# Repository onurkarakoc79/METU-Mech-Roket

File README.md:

# METU Mech Rocket Team Electronic Cards and Codes
This repository contains the electronic codes and card designs for the METU Mech Rocket Team's rocket system. The system consists of two card designs, each equipped with an Arduino Due controller.

## Communication Card
The first Arduino Due is responsible for communication and utilizes the following modules:

SX1262 LoRa module
SIM800L module
CH376S USB module
The communication card enables data transfer with the ground station. The SX1262 LoRa module and SIM800L module are used for wireless communication, while the CH376S USB module handles data storage to a USB device.

## Processor Card
The second Arduino Due is responsible for data processing and incorporates the following components:

BME280 sensor
Dallas temperature sensor
BMP180 sensor
NEO M8N GPS module
Parachute opening system (controlled by a servo and a transistor that fires the gas tank)
The processor card collects data related to humidity, temperature, altitude, and absolute location. It supports two sensors for each type of data, such as BME280 and BMP180. The collected data is processed using a Kalman filter algorithm for improved accuracy. The processed data is then transferred to the communication card via serial communication.

## Card Designs
This repository also includes the necessary files for the card designs. The provided KiCad files contain the card designs and necessary footprints. To use the designs, add the footprint files to KiCad in the appropriate manner. The card designs have been configured for use with either Arduino Due or Arduino Mega Due, based on the pin configuration.

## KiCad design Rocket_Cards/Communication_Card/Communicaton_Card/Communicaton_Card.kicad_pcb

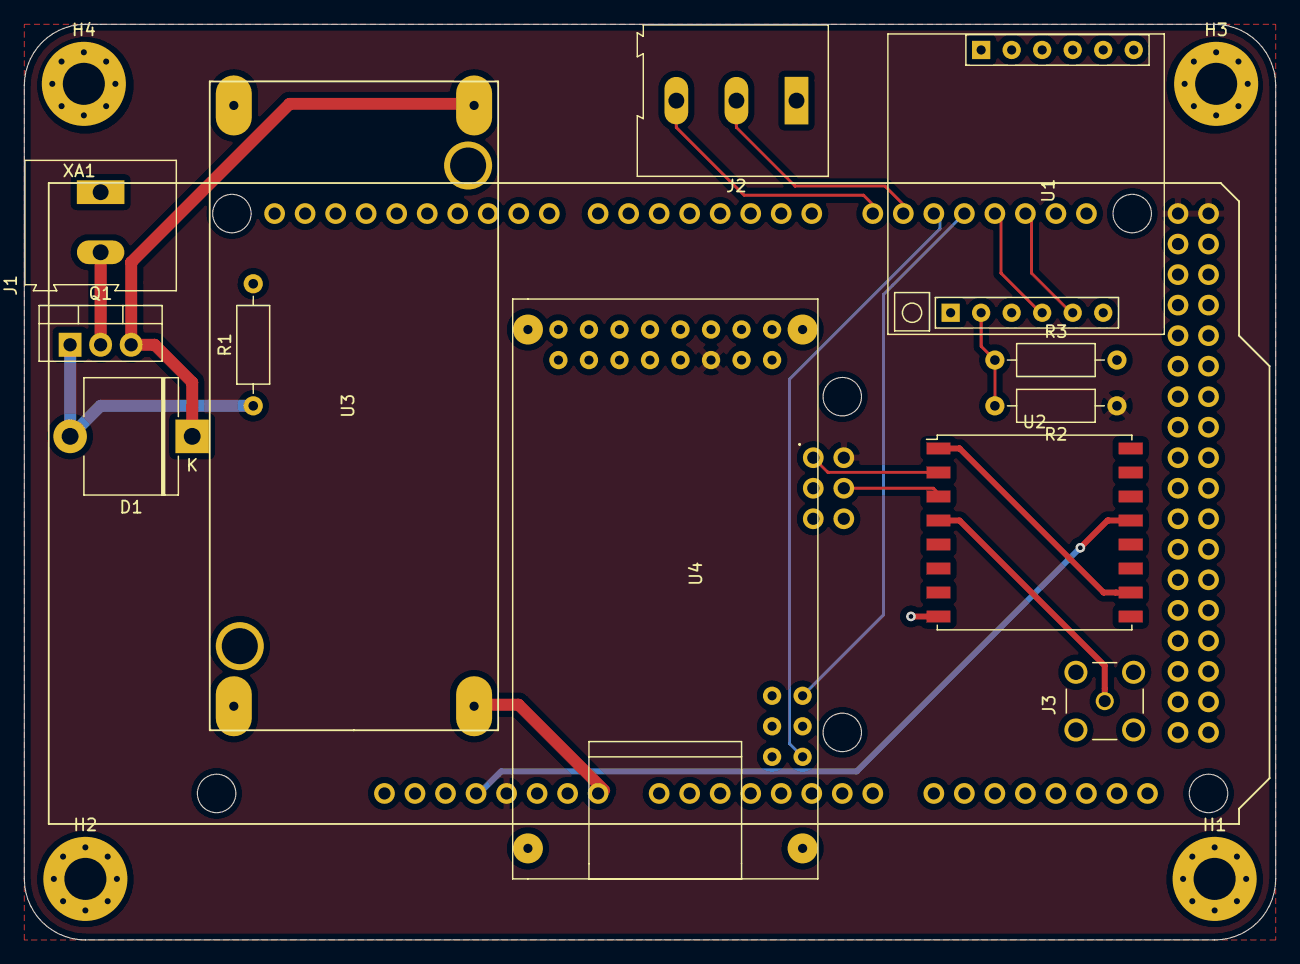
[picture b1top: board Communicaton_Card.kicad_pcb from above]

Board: 2 copper layers, 104.1 x 76.2 mm, 17 parts (0 on the bottom side), 18 nets.

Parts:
D1: D_Zener; D_5KP_P10.16mm_Horizontal
H1, H2, H3, H4: MountingHole_Pad; MountingHole_3.5mm_Pad_Via
J1: POWER_CONN; TerminalBlock_Altech_AK300-2_P5.00mm
J2: Serial_Comm; TerminalBlock_Altech_AK300-3_P5.00mm
J3: SMA_CONNECTOR; LPRS_SMA_CONNECTOR
Q1: P_Channel MOSFET; TO-220-3_Vertical
R1: 100K; R_Axial_DIN0207_L6.3mm_D2.5mm_P10.16mm_Horizontal
R2: 1 OHM; R_Axial_DIN0207_L6.3mm_D2.5mm_P10.16mm_Horizontal
R3: 4 OHM; R_Axial_DIN0207_L6.3mm_D2.5mm_P10.16mm_Horizontal
U1: Sim800L_Sch; Sim800L
U2: RFM95W-868S2; HOPERF_RFM9XW_SMD
U3: XL4015; XL4015_Converter
U4: CH376S_USB_MODULE; CH376_USB_Foot
XA1: Arduino_Mega2560_Shield

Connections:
+3V3: U2.13, XA1.3V3
+5V: R2.1, U4.1, XA1.5V1, XA1.5V2, XA1.5V3, XA1.5V4
+12V: U3.3, XA1.VIN
+24V: D1.1, Q1.3, U3.1
Antenna: J3.1, U2.4
CH376_RX: U4.4, XA1.D16
CH376_TX: U4.3, XA1.D17
GND: H1.1, H2.1, H3.1, H4.1, J1.1, J2.1, J3.G1, J3.G2, J3.G3, J3.G4, R1.2, R3.2, U1.6, U2.8, U3.2, U3.4, U4.2, XA1.GND1, XA1.GND2, XA1.GND3, XA1.GND4, XA1.GND5, XA1.GND6
LoRa_MISO: U2.2, XA1.MISO
LoRa_MOSI: U2.3, XA1.MOSI
unnamed: D1.2, Q1.1, R1.1
unnamed: J1.2, Q1.2
unnamed: R2.2, R3.1, U1.2
unnamed: U2.1, U2.10
Proccessor_Card_RXD: J2.3, XA1.D14
Proccessor_Card_TXD: J2.2, XA1.D15
Sim800_RXD: U1.4, XA1.D18
Sim800_TXD: U1.5, XA1.D19

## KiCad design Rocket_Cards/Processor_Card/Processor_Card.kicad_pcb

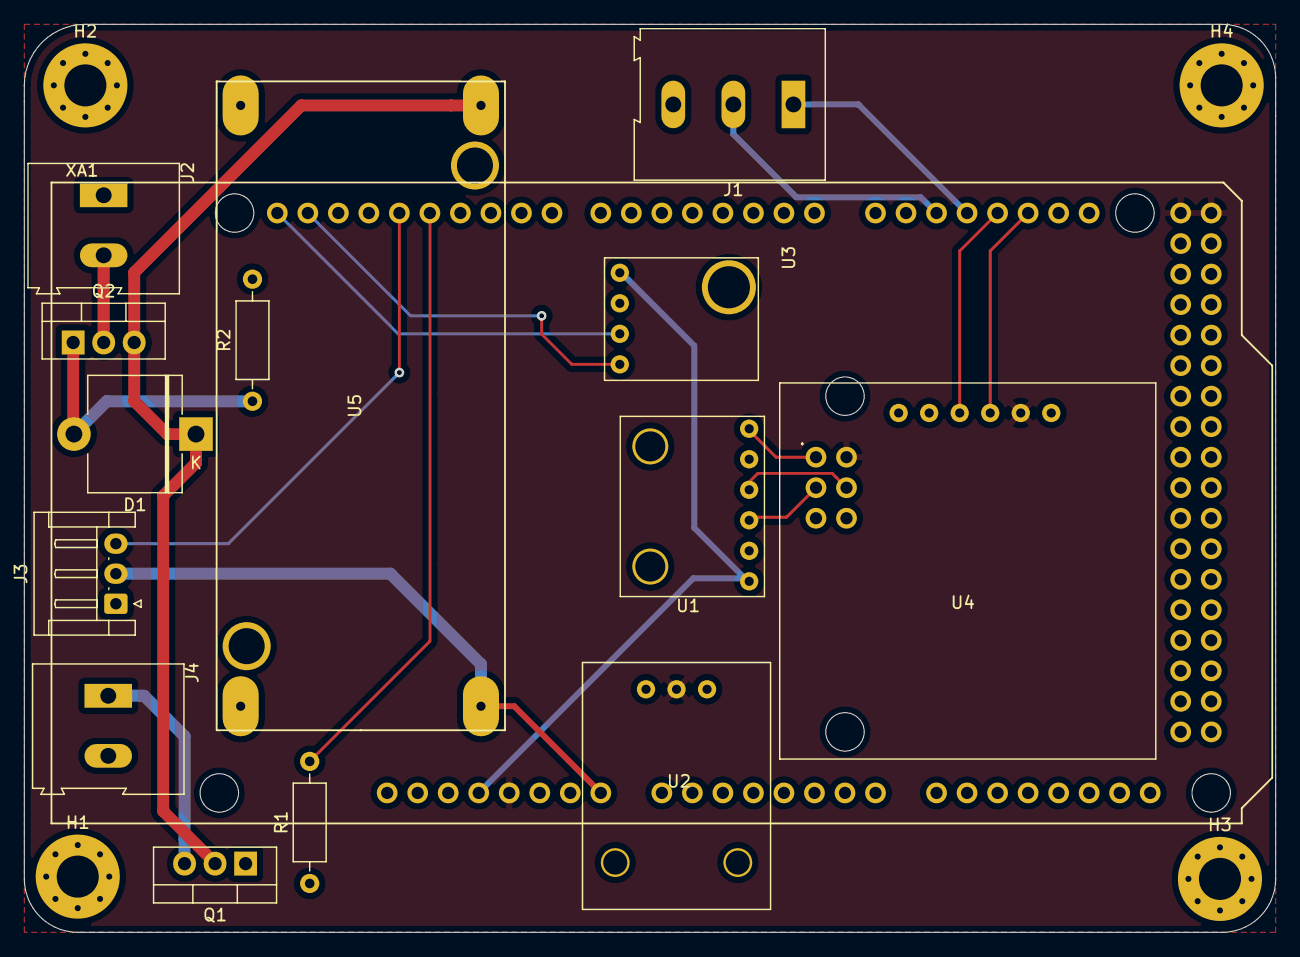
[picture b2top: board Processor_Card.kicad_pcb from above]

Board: 2 copper layers, 104.1 x 75.6 mm, 19 parts (0 on the bottom side), 20 nets.

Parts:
D1: D_Zener; D_5KP_P10.16mm_Horizontal
H1, H2, H3, H4: MountingHole_Pad; MountingHole_3.5mm_Pad_Via
J1: Screw_Terminal_01x03; TerminalBlock_Altech_AK300-3_P5.00mm
J2: POWER_CONN; TerminalBlock_Altech_AK300-2_P5.00mm
J3: Recovery_System_Servo; JST_EH_S3B-EH_1x03_P2.50mm_Horizontal
J4: Recovery_System_Conn; TerminalBlock_Altech_AK300-2_P5.00mm
Q1: Rcovery_System_GAS; TO-220-3_Vertical
Q2: IRF4905; TO-220-3_Vertical
R1: 10k; R_Axial_DIN0207_L6.3mm_D2.5mm_P10.16mm_Horizontal
R2: 100k; R_Axial_DIN0207_L6.3mm_D2.5mm_P10.16mm_Horizontal
U1: BME280; BME280_3.3
U2: DS18B20
U3: BMP180
U4: NEO_M8N; Neo_M8N
U5: XL4015; XL4015_Converter
XA1: Arduino_Mega2560_Shield

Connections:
+3V3: U1.1, U3.1, XA1.3V3
+5V: U2.2, U4.5, XA1.5V1, XA1.5V2, XA1.5V3, XA1.5V4
+12V: J3.2, U5.3, XA1.VIN
+24V: D1.1, Q1.2, Q2.3, U5.1
BME_MISO: U1.6, XA1.MISO
BME_MOSI: U1.4, XA1.MOSI
BME_SCK: U1.3, XA1.SCK
BMP_SCL: U3.3, XA1.SCL
BMP_SDA: U3.4, XA1.SDA
Communicaton_Card_RXD: J1.2, XA1.D16
Communicaton_Card_TXD: J1.1, XA1.D17
GND: H1.1, H2.1, H3.1, H4.1, J1.3, J2.1, J3.1, J4.2, R2.2, U1.2, U2.1, U3.2, U4.6, U5.2, U5.4, XA1.GND1, XA1.GND2, XA1.GND3, XA1.GND4, XA1.GND5, XA1.GND6
GPS_RXD: U4.3, XA1.D18
GPS_TXD: U4.4, XA1.D19
Gas_Recovery_Data: R1.2, XA1.D12
unnamed: D1.2, Q2.1, R2.1
unnamed: J2.2, Q2.2
unnamed: J4.1, Q1.3
unnamed: Q1.1, R1.1
Servo_Control: J3.3, XA1.D13

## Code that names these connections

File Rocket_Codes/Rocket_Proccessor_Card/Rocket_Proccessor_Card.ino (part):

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////////////////////////////////////////////////////////////////////////BME SPI DEFINES STARTS////////////////////////////////////////////////////////////////////////////////////


static const uint8_t BME_SCK=13;    // SCL to Pin 13 Arduino UNO
static const uint8_t BME_MISO=12;   // SDO to Pin 12
static const uint8_t BME_MOSI=11;   // SDA to Pin 11 
static const uint8_t BME_CS=5;     // CSB to Pin 10
static const uint8_t BME_Addresses=0x77;
static const float SEALEVELPRESSURE_HPA=1013.25;
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
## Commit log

2022-11-10 Create Rocket_Codes
